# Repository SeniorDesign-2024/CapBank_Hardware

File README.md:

# CapBank_Hardware
PCB design files for the capacitor bank board

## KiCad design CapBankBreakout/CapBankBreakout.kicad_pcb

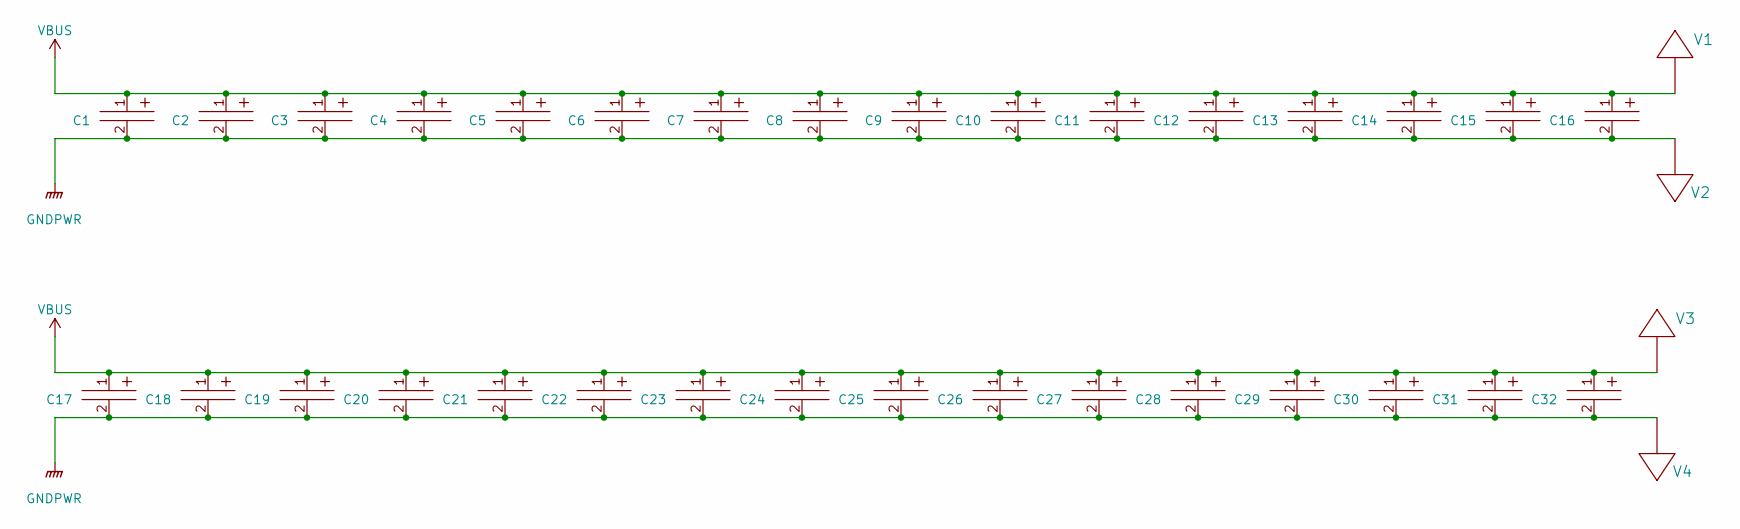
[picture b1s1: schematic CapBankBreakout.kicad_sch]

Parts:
C1, C2, C3, C4, C5, C6, C7, C8, C9, C10, C11, C12, C13, C14, C15, C16, C17, C18, C19, C20, C21, C22, C23, C24, C25, C26, C27, C28, C29, C30, C31, C32: PCAP_ALF70_C_EH_KEM
V1, V2, V3, V4: BATT_PWR_VIA; via

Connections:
GNDPWR: C1.2, C2.2, C3.2, C4.2, C5.2, C6.2, C7.2, C8.2, C9.2, C10.2, C11.2, C12.2, C13.2, C14.2, C15.2, C16.2, C17.2, C18.2, C19.2, C20.2, C21.2, C22.2, C23.2, C24.2, C25.2, C26.2, C27.2, C28.2, C29.2, C30.2, C31.2, C32.2, V2.1, V4.1
VBUS: C1.1, C2.1, C3.1, C4.1, C5.1, C6.1, C7.1, C8.1, C9.1, C10.1, C11.1, C12.1, C13.1, C14.1, C15.1, C16.1, C17.1, C18.1, C19.1, C20.1, C21.1, C22.1, C23.1, C24.1, C25.1, C26.1, C27.1, C28.1, C29.1, C30.1, C31.1, C32.1, V1.1, V3.1

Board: 2 copper layers, 42 parts (0 on the bottom side), 2 nets, no tracks yet.

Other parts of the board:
J**: CAP_SIDE_1
mouse-bite-5mm-slot, mouse-bite-5mm-slot#2, mouse-bite-5mm-slot#3, mouse-bite-5mm-slot#4, mouse-bite-5mm-slot#5: VAL**; mouse-bite-5mm-slot

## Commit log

2024-02-01 PCB edit 1
    caps added, waiting on mounting hole dfx from evan
2024-02-18 commit 2
    hi brady
2024-02-19 commit 3
2024-02-22 redesign 1
    mouse bites inserted.
2024-02-26 board review changes made
    rounded corners, cosmetic changes
2024-02-27 generated gerbs
2024-02-27 remade gerbs, included right side holes
2024-02-27 holes added and double board generated
2024-02-27 old gerbs removed
2024-02-27 single and double board configs generated in main branch
    current PCB layout reflects single board layout. Pull the Double-Board branch to work with both sides.
2024-02-29 capbreakout board STEP files added
